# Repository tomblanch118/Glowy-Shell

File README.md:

# Glowy-Shell
Code, documents, circuits and schematics for the glowy shell project.

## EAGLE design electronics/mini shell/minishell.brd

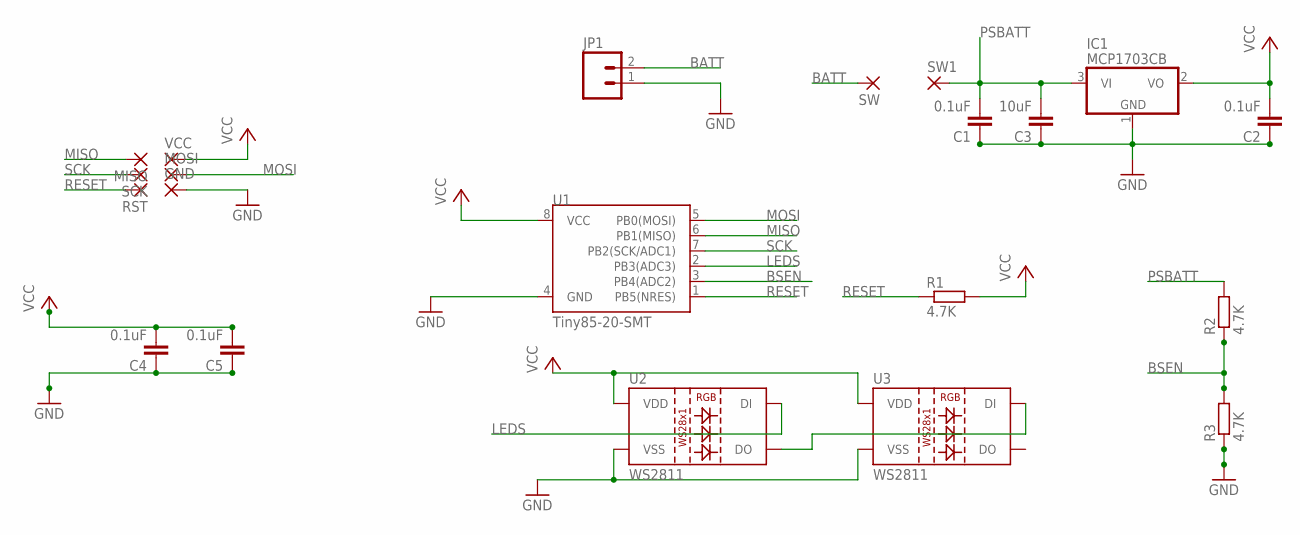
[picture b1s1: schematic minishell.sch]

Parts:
C1, C2, C4, C5: 0.1uF; C0603
C3: 10uF; C0805
GND: SMD2; SMD1,27-2,54
IC1: MCP1703CB; SOT23
JP1: M02PTH; 1X02
MISO: SMD2; SMD1,27-2,54
MOSI: SMD2; SMD1,27-2,54
R1, R2, R3: 4.7K; R0603
RST: SMD2; SMD1,27-2,54
SCK: SMD2; SMD1,27-2,54
SW, SW1: SMD2; SMD1,27-2,54
U1: Tiny85-20-SMT; SO08-EIAJ
U2, U3: WS2811; LED-TRICOLOR-5050-IC
VCC: SMD2; SMD1,27-2,54

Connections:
BATT: JP1.2, SW.1
BSEN: R2.1, R3.2, U1.3 (PB4(ADC2))
GND: C1.1, C2.1, C3.1, C4.1, C5.1, GND.1, IC1.1 (GND), JP1.1, R3.1, U1.4 (GND), U2.6 (VSS), U3.6 (VSS)
LEDS: U1.2 (PB3(ADC3)), U2.2 (DI)
MISO: MISO.1, U1.6 (PB1(MISO))
MOSI: MOSI.1, U1.5 (PB0(MOSI))
unnamed: U2.1 (DO), U3.2 (DI)
PSBATT: C1.2, C3.2, IC1.3 (VI), R2.2, SW1.1
RESET: R1.1, RST.1, U1.1 (PB5(NRES))
SCK: SCK.1, U1.7 (PB2(SCK/ADC1))
VCC: C2.2, C4.2, C5.2, IC1.2 (VO), R1.2, U1.8 (VCC), U2.3 (VDD), U2.5 (VDD), U3.3 (VDD), U3.5 (VDD), VCC.1

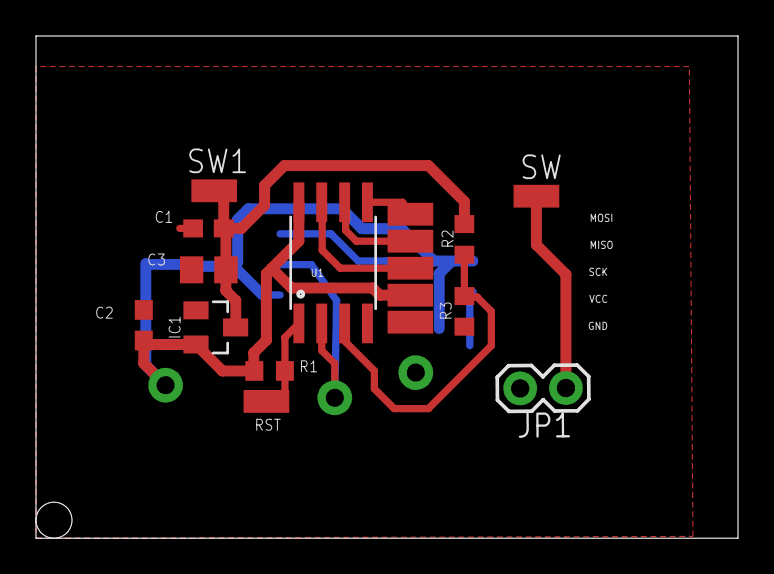
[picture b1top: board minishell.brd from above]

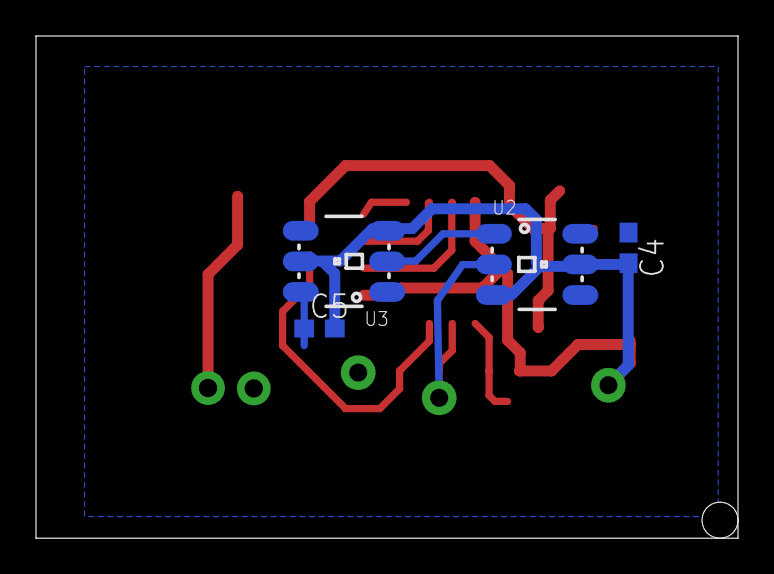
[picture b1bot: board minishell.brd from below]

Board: 2 copper layers, 39.0 x 27.9 mm, 21 parts (4 on the bottom side), 11 nets.

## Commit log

2015-12-19 Initial electronics commit
    Initial commit of schematics and board layout for glowy shell
    electronics.

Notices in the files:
parts and their libraries:
SparkFun-Connectors: Licensing: Creative Commons ShareAlike 4.0 International - https://creativecommons.org/licenses/by-sa/4.0
